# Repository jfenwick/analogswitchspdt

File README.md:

# analogswitchspdt

I was trying to learn how to control a servo using a blue pill. The servo requires external power because it needs more amps than what the USB port on my PC can handle. The programmer cable for the board should also not be plugged into the computer at the same time as the external power supply. This means every time I want to program I have to disconnect the servo and the external power supply before plugging in the programmer, and vice versa. This is a board I'm attempting to make in KiCAD that has some DG412 Quad SPST CMOS Analog Switches connected to the two sides. A SPDT switch makes it so I can switch which one is currently active. This means no unplugging, just hitting the toggle switch.

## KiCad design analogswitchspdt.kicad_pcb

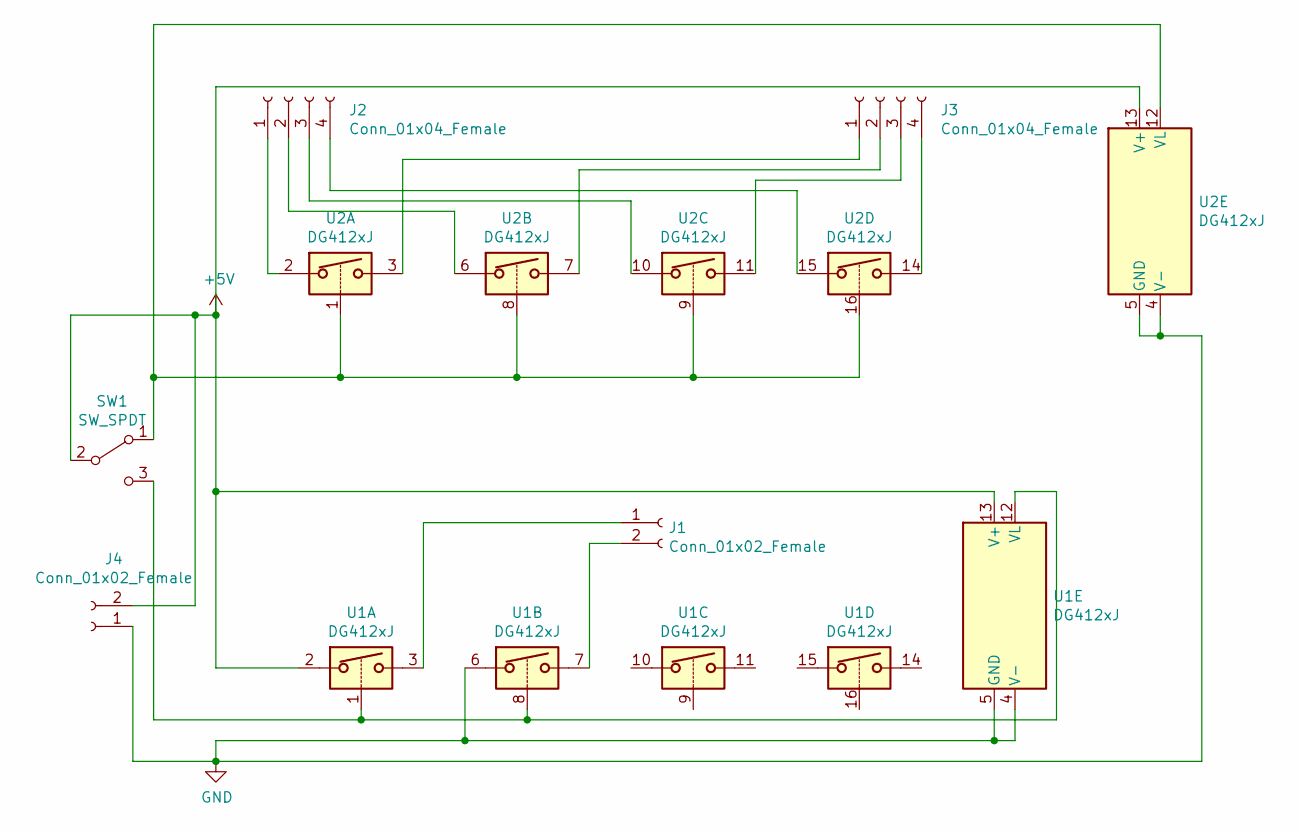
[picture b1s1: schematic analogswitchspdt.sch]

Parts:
J1, J4: Conn_01x02_Female; PinHeader_1x02_P2.54mm_Vertical
J2, J3: Conn_01x04_Female; PinHeader_1x04_P2.54mm_Vertical
SW1: SW_SPDT; MTS_SPDT
U1, U2: DG412xJ; DIP-16_W7.62mm

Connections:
+5V: J4.2, SW1.2 (B), U1.2, U1.13 (V+), U2.13 (V+)
GND: J4.1, U1.4 (V-), U1.5 (GND), U1.6, U2.4 (V-), U2.5 (GND)
unnamed: J1.1, U1.3
unnamed: J1.2, U1.7
unnamed: J2.1, U2.2
unnamed: J2.2, U2.6
unnamed: J2.3, U2.10
unnamed: J2.4, U2.15
unnamed: J3.1, U2.3
unnamed: J3.2, U2.7
unnamed: J3.3, U2.11
unnamed: J3.4, U2.14
unnamed: SW1.1 (A), U2.1, U2.8, U2.9, U2.12 (VL), U2.16
unnamed: SW1.3 (C), U1.1, U1.8, U1.12 (VL)

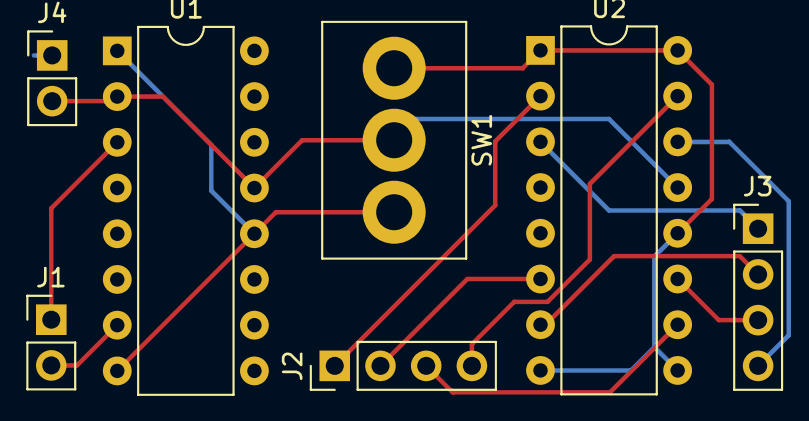
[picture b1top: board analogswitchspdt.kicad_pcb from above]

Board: 2 copper layers, 7 parts (0 on the bottom side), 14 nets.

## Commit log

2021-03-23 Intent of project stated.
2021-03-23 Updated doc error.
